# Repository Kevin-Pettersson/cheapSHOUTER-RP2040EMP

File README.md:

# cheapSHOUTER-RP2040EMP
Improved version of the great ChipSHOUTER-PicoEMP, this version has made cuts to the BOM and has added functionality inclduing: built in RP2040 instead of using a PICO, USB-C, LIPO charger + protection, USB isolation (not true isolation, allows to disconnect VBUS) + TVS diodes, buzzer, cleaner layout, and more.

## Contributors
- Colin O'Flynn (original HW design)
- Nezza (original FW)
- Kevin Pettersson 
- Linus Backlund
- Wilhelm Westermark

## Firmware
The firmware is a slightly tweaked version of the c-firmware from the original repo. The changes adapts the button logic to the active-high board design and activates the buzzer for a short period upon manual pulses.

## License

This work is licensed under a [Creative Commons Attribution-ShareAlike 3.0 International License][cc-by-sa].

[cc-by-sa]: http://creativecommons.org/licenses/by-sa/3.0/
[cc-by-sa-image]: https://licensebuttons.net/l/by-sa/3.0/88x31.png
[cc-by-sa-shield]: https://img.shields.io/badge/License-CC%20BY--SA%203.0-lightgrey.svg

ChipSHOUTER is a trademark of NewAE Technology Inc., registered in the US, European Union, and other jurisdictions.
PicoEMP is a trademark of NewAE Technology Inc.

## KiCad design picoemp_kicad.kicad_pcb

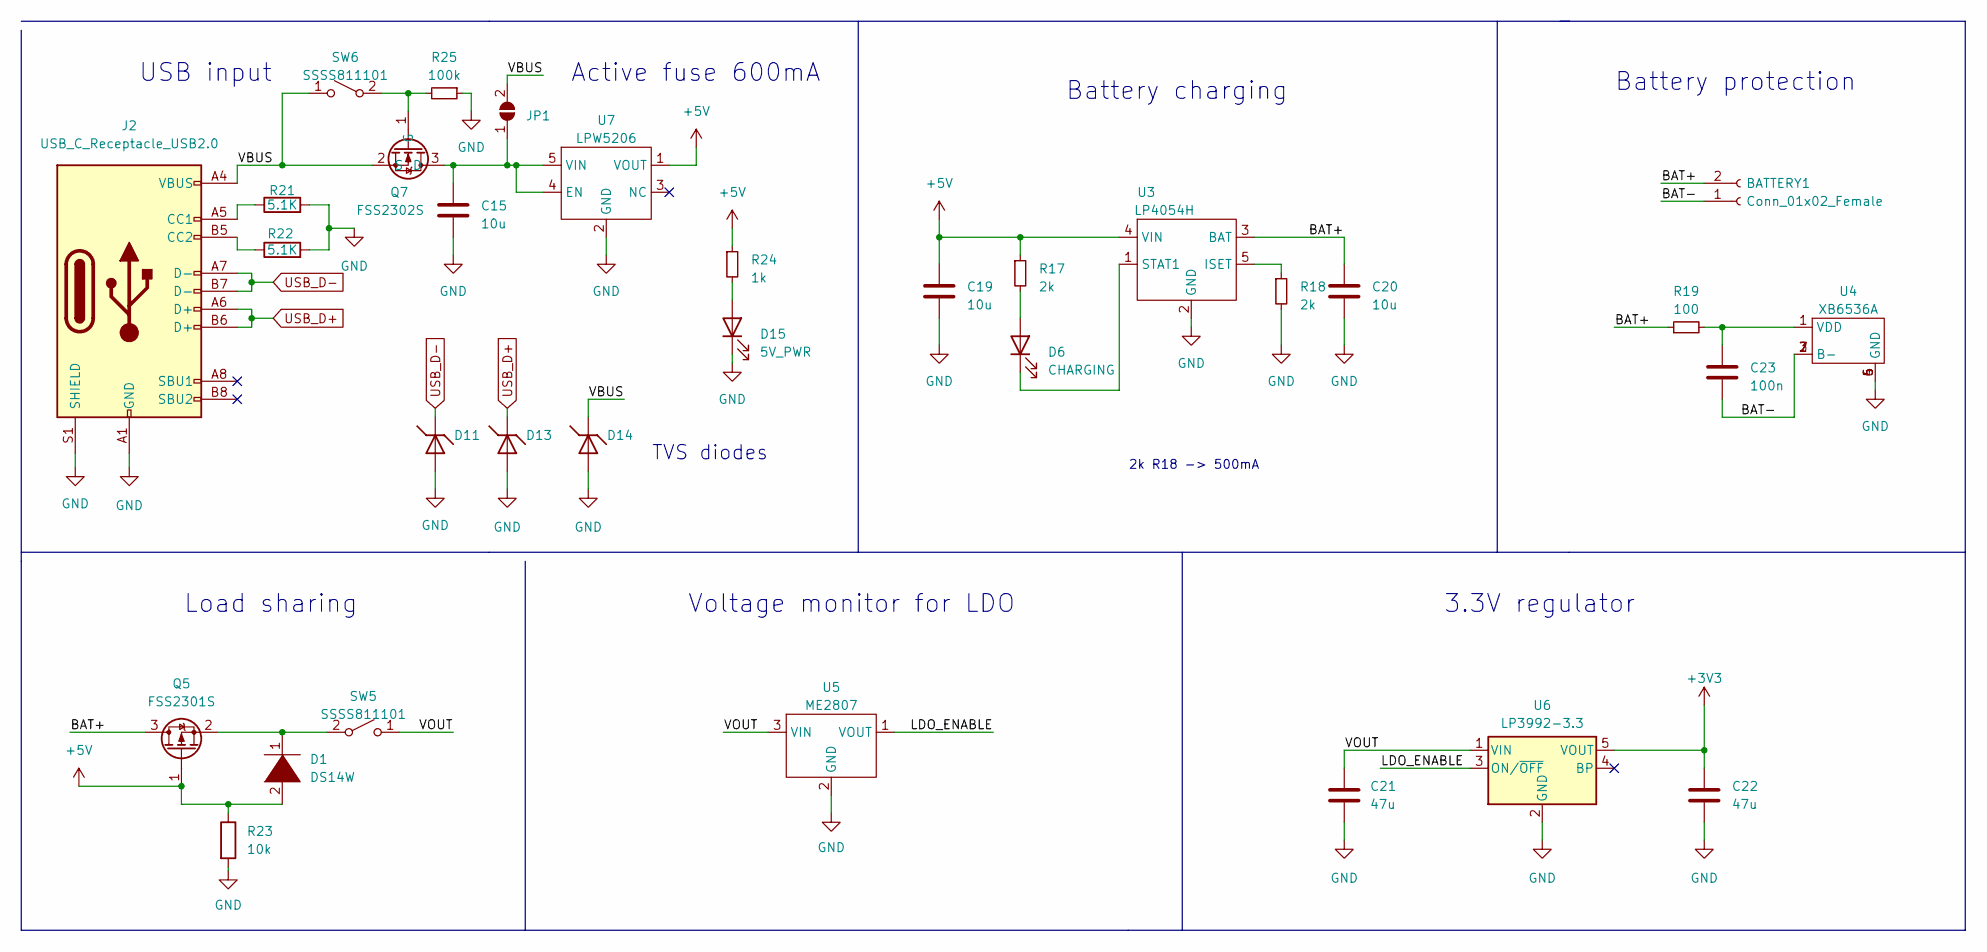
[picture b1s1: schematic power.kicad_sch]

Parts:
BATTERY1: Conn_01x02_Female; JST_PH_S2B-PH-K_1x02_P2.00mm_Horizontal
C15, C19, C20: 10u; C_0603_1608Metric
C21, C22: 47u; C_0805_2012Metric
C23: 100n; C_0603_1608Metric
D1: DS14W; D_SOD-123F
D6: CHARGING; LED_0603_1608Metric
D11, D13: LESD9L5.0T5G; D_SOD-923
D14: PESDNC5D7VU; D_SOD-523
D15: 5V_PWR; LED_0603_1608Metric
J2: USB_C_Receptacle_USB2.0; USB_C_Receptacle_HRO_TYPE-C-31-M-12; JLCPCB Part # C709357
JP1: SolderJumper-2_P1.3mm_Open_Pad1.0x1.5mm
Q5: FSS2301S; SOT-23
Q7: FSS2302S; SOT-23
R17, R18: 2k; R_0603_1608Metric
R19: 100; R_0603_1608Metric
R21: 5.1K; R_0603_1608Metric; JLCPCB Part # C23186
R22: 5.1K; R_0603_1608Metric
R23: 10k; R_0603_1608Metric
R24: 1k; R_0603_1608Metric
R25: 100k; R_0603_1608Metric
SW5, SW6: SSSS811101; SW_SPDT_PCM12
U3: LP4054H; SOT-23-5
U4: XB6536A; DFN-6-1EP_2x2mm_P0.65mm_EP1x1.6mm
U5: ME2807; SOT-23-3
U6: LP3992-3.3; SOT-23-5
U7: LPW5206; SOT-23-5

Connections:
+5V: C19.1, D1.2 (K), Q5.1 (G), R17.1, R23.1, R24.1, U3.4 (VIN), U7.1 (VOUT)
/Power/BAT+: BATTERY1.2 (Pin_1), C20.1, Q5.3 (D), R19.1, U3.3 (BAT)
/Power/BAT-: BATTERY1.1 (Pin_2), C23.2, U4.2 (B-), U4.3 (B-), U4.7 (B-)
/Power/LDO_ENABLE: U5.1 (VOUT), U6.3 (ON/~OFF)
/Power/VBUS: D14.1 (K), J2.A4 (VBUS), J2.A9 (VBUS), J2.B4 (VBUS), J2.B9 (VBUS), JP1.2 (B), Q7.2 (S), SW6.1 (B)
/Power/VOUT: C21.1, SW5.1 (B), U5.3 (VIN), U6.1 (VIN)
GND: C15.2, C19.2, C20.2, C21.2, C22.2, D11.2 (A), D13.2 (A), D14.2 (A), D15.1 (K), J2.A1 (GND), J2.A12 (GND), J2.B1 (GND), J2.B12 (GND), J2.S1 (SHIELD), R18.2, R21.2, R22.2, R23.2, R25.1, U3.2 (GND), U4.4 (GND), U4.5 (GND), U4.6 (GND), U5.2 (GND), U6.2 (GND), U7.2 (GND); also elsewhere on the board
unnamed: D1.1 (A), Q5.2 (S), SW5.2 (A)
unnamed: D6.2 (A), R17.2
unnamed: D6.1 (K), U3.1 (STAT1)
unnamed: D15.2 (A), R24.2
unnamed: J2.A5 (CC1), R21.1
unnamed: J2.B5 (CC2), R22.1
unnamed: Q7.1 (G), R25.2, SW6.2 (A)
unnamed: R18.1, U3.5 (ISET)
unnamed: C23.1, R19.2, U4.1 (VDD)
USB_D+: D13.1 (K), J2.A6 (D+), J2.B6 (D+); also elsewhere on the board
USB_D-: D11.1 (K), J2.A7 (D-), J2.B7 (D-); also elsewhere on the board

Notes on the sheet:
2k R18 -> 500mA
Battery protection
USB input
Battery charging
Voltage monitor for LDO
Active fuse 600mA
TVS diodes
3.3V regulator
Load sharing

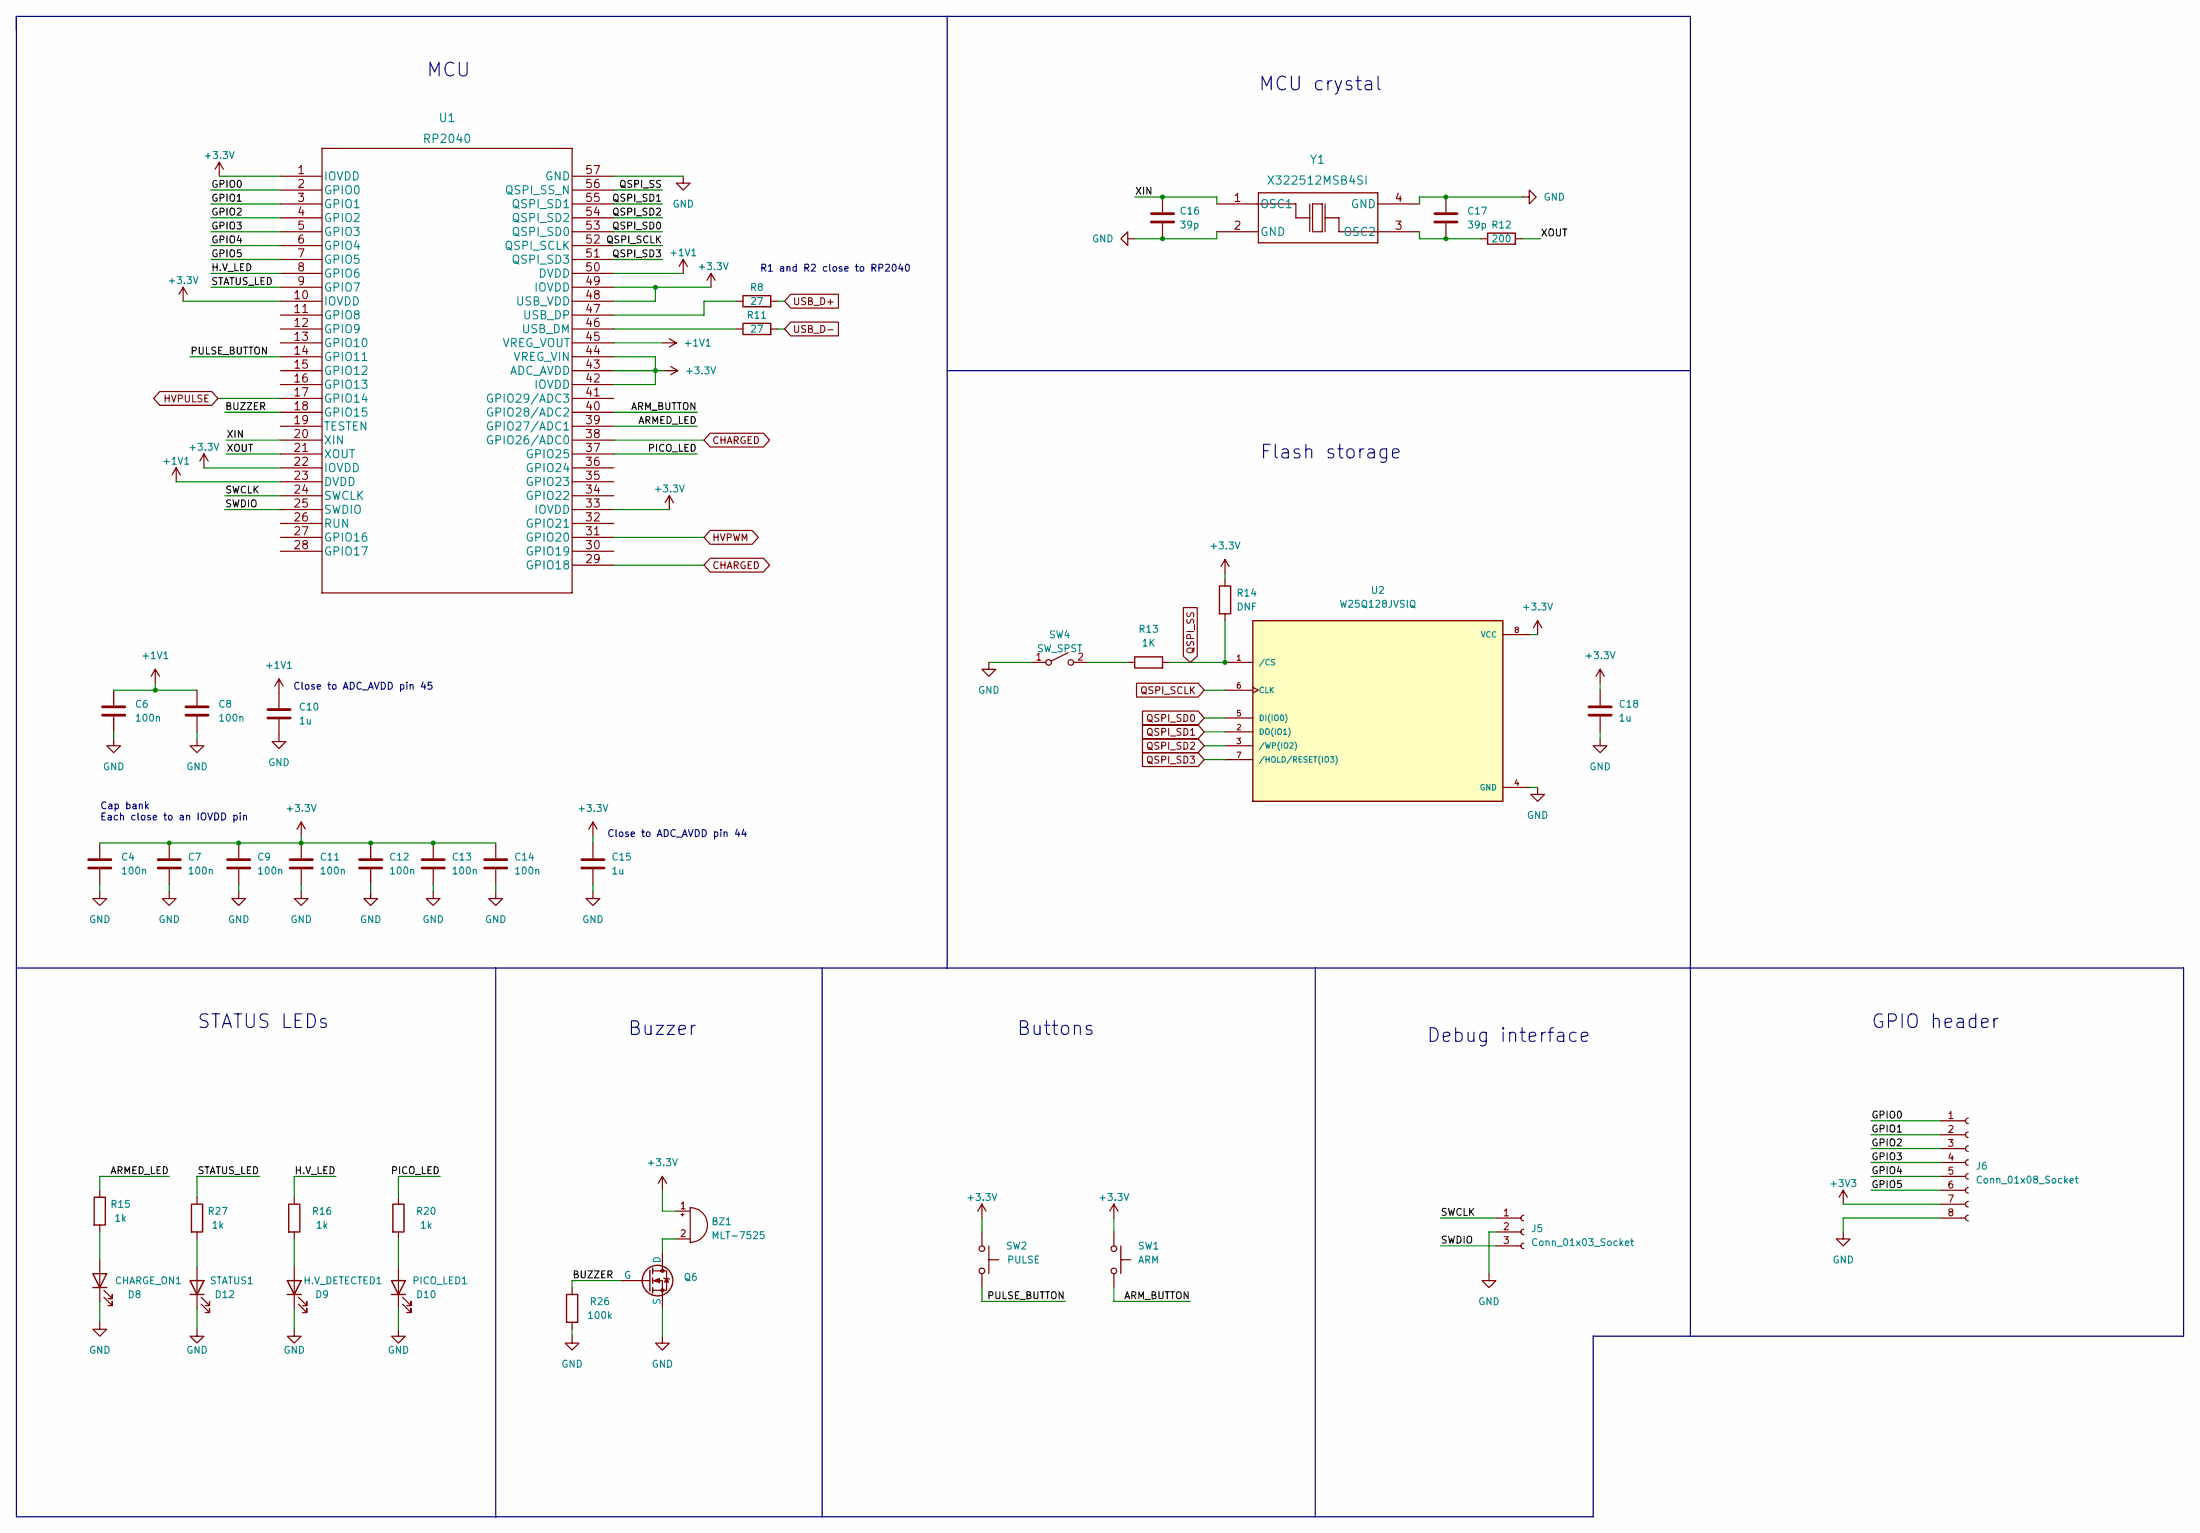
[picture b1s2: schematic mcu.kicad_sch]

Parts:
BZ1: MLT-7525; PUIAudio_SMT_0825_S_4_R
C4, C6, C7, C8, C9, C11, C12, C13, C14: 100n; C_0603_1608Metric
C10, C15, C18: 1u; C_0603_1608Metric
C16, C17: 39p; C_0603_1608Metric
D8: CHARGE_ON1; LED_0603_1608Metric
D9: H.V_DETECTED1; LED_0603_1608Metric
D10: PICO_LED1; LED_0603_1608Metric
D12: STATUS1; LED_0603_1608Metric
J5: Conn_01x03_Socket; PinHeader_1x03_P2.54mm_Vertical
J6: Conn_01x08_Socket; PinSocket_1x08_P2.54mm_Vertical
Q6: FSS2302S; SOT-23
R8, R11: 27; R_0603_1608Metric
R12: 200; R_0603_1608Metric
R13: 1K; R_0603_1608Metric
R14: DNF
R15, R16, R20, R27: 1k; R_0603_1608Metric
R26: 100k; R_0603_1608Metric
SW1: ARM
SW2: PULSE
SW4: SW_SPST; SW_SPST_CK_RS282G05A3
U1: RP2040; QFN-56-1EP_7x7mm_P0.4mm_EP3.2x3.2mm; JLCPCB Part # C2040
U2: W25Q128JVSIQ; IC_W25Q16JVUXIQ_TR; PARTREV I
Y1: X322512MSB4SI

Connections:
+1V1: C6.1, C8.1, C10.1, U1.23 (DVDD), U1.45 (VREG_VOUT), U1.50 (DVDD)
/RP2040/ARMED_LED: R15.1, U1.39 (GPIO27/ADC1)
/RP2040/ARM_BUTTON: SW1.1, U1.40 (GPIO28/ADC2)
/RP2040/BUZZER: Q6.1 (G), R26.1, U1.18 (GPIO15)
/RP2040/GPIO0: J6.1, U1.2 (GPIO0)
/RP2040/GPIO1: J6.2, U1.3 (GPIO1)
/RP2040/GPIO2: J6.3, U1.4 (GPIO2)
/RP2040/GPIO3: J6.4, U1.5 (GPIO3)
/RP2040/GPIO4: J6.5, U1.6 (GPIO4)
/RP2040/GPIO5: J6.6, U1.7 (GPIO5)
/RP2040/H.V_LED: R16.1, U1.8 (GPIO6)
/RP2040/PICO_LED: R20.1, U1.37 (GPIO25)
/RP2040/PULSE_BUTTON: SW2.2, U1.14 (GPIO11)
/RP2040/STATUS_LED: R27.1, U1.9 (GPIO7)
/RP2040/SWCLK: J5.1, U1.24 (SWCLK)
/RP2040/SWDIO: J5.3, U1.25 (SWDIO)
/RP2040/XIN: C16.1, U1.20 (XIN), Y1.1 (OSC1)
CHARGED: U1.29 (GPIO18), U1.38 (GPIO26/ADC0); also elsewhere on the board
GND: C4.2, C6.2, C7.2, C8.2, C9.2, C10.2, C11.2, C12.2, C13.2, C14.2, C15.2, C16.2, C17.1, C18.2, D8.1 (K), D9.1 (K), D10.1 (K), D12.1 (K), J5.2, J6.8, Q6.2 (S), R26.2, SW4.1 (A), U1.57 (GND), U2.4 (GND), Y1.2 (GND), Y1.4 (GND); also elsewhere on the board
HVPULSE: U1.17 (GPIO14); also elsewhere on the board
HVPWM: U1.31 (GPIO20); also elsewhere on the board
unnamed: BZ1.2 (-), Q6.3 (D)
unnamed: D8.2 (A), R15.2
unnamed: D9.2 (A), R16.2
unnamed: D10.2 (A), R20.2
unnamed: D12.2 (A), R27.2
unnamed: R13.1, SW4.2 (B)
unnamed: R11.1, U1.46 (USB_DM)
unnamed: R8.1, U1.47 (USB_DP)
QSPI_SCLK: U1.52 (QSPI_SCLK), U2.6 (CLK)
QSPI_SD0: U1.53 (QSPI_SD0), U2.5 (DI(IO0))
QSPI_SD1: U1.55 (QSPI_SD1), U2.2 (DO(IO1))
QSPI_SD2: U1.54 (QSPI_SD2), U2.3 (/WP(IO2))
QSPI_SD3: U1.51 (QSPI_SD3), U2.7 (/HOLD/RESET(IO3))
USB_D+: R8.2; also elsewhere on the board
USB_D-: R11.2; also elsewhere on the board

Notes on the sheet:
Cap bank Each close to an IOVDD pin
R1 and R2 close to RP2040
Buttons
MCU crystal
MCU
STATUS LEDs
Close to ADC_AVDD pin 45
Debug interface
Buzzer
Flash storage
Close to ADC_AVDD pin 44
GPIO header

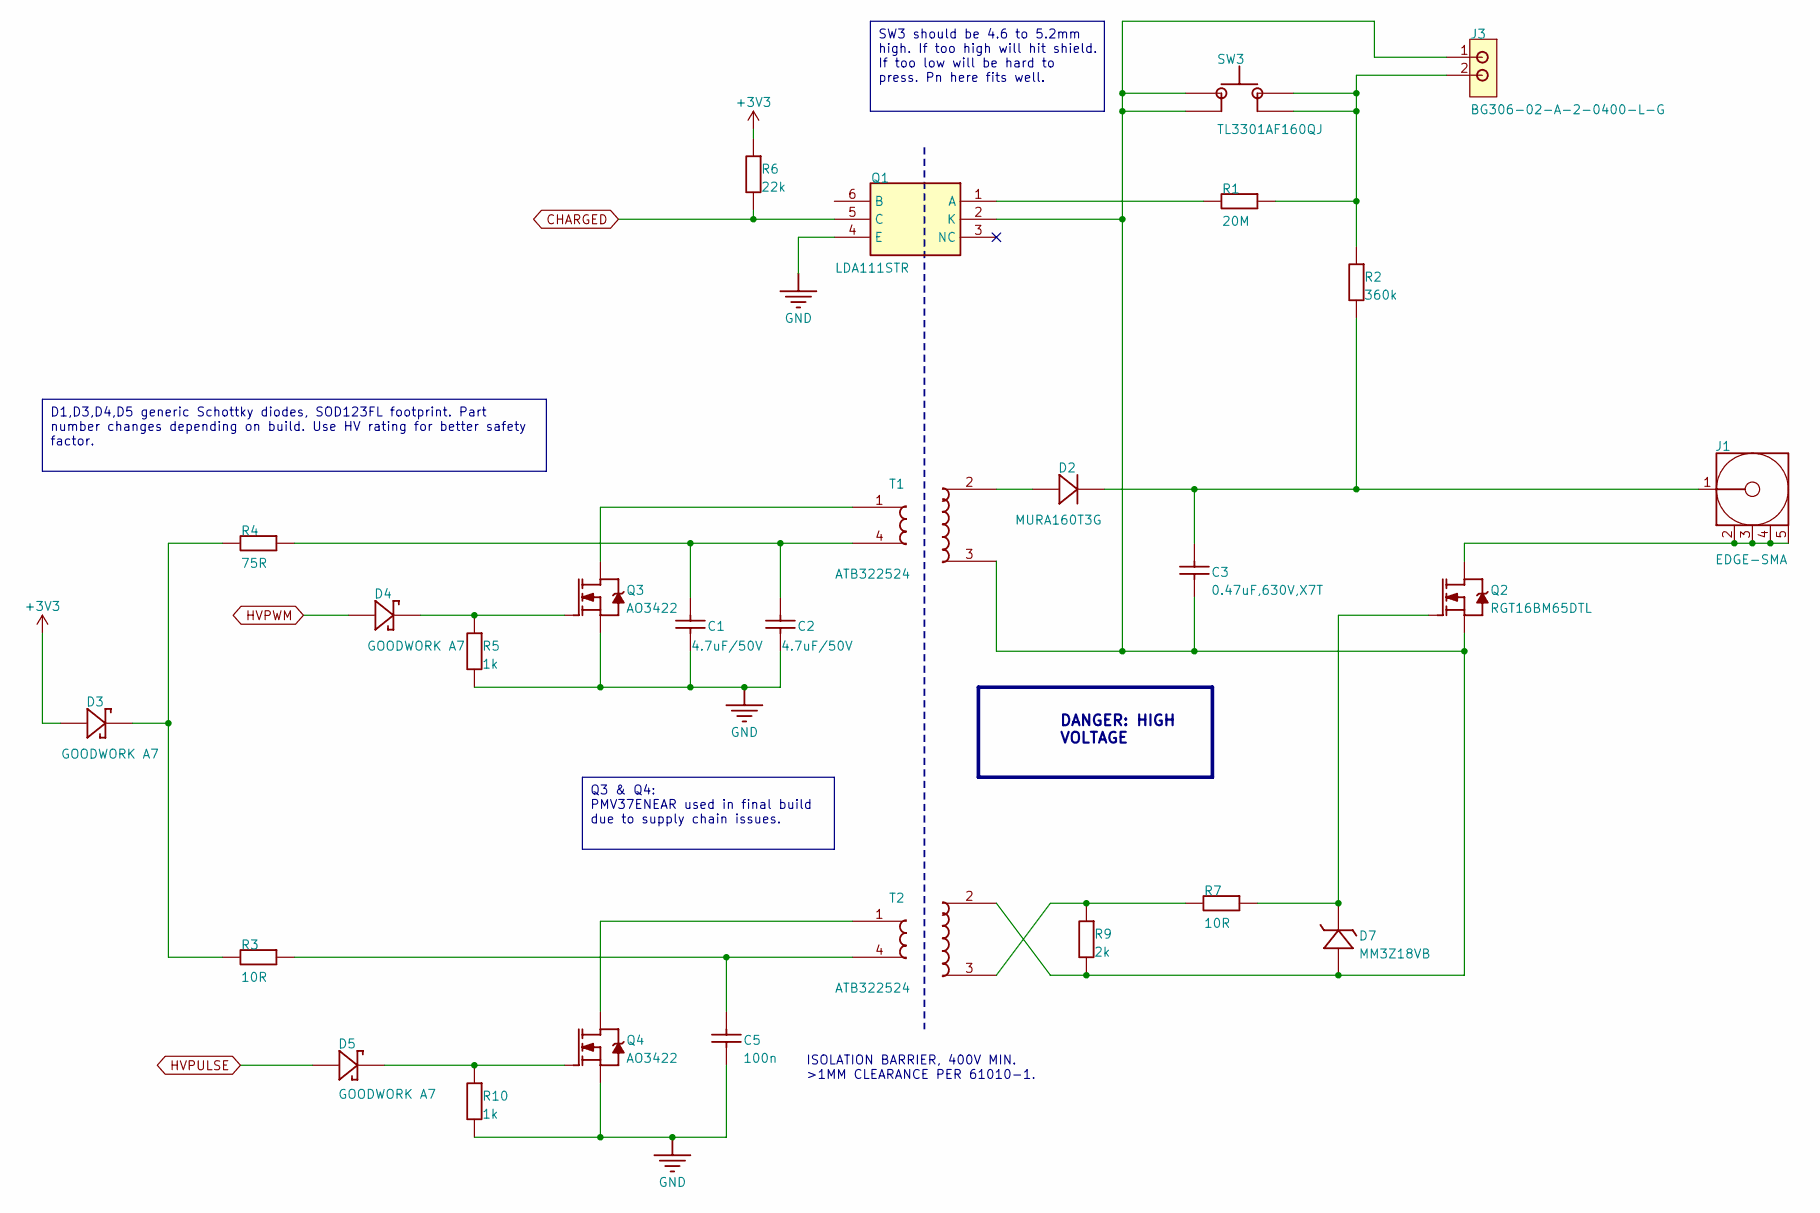
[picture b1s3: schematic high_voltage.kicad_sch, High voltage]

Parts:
C1, C2: 4.7uF/50V; CAPC0805_M; RATED VOLTAGE 50VDC; TOLERANCE 10%; PART NUMBER CCHIP-4u7-0805-50V
C3: 0.47uF,630V,X7T; C_2220_5650Metric; RATED VOLTAGE 630V; TOLERANCE +22/-30; PART NUMBER KRM55TR72J474MH01K
C5: 100n; CAPC0603_M; RATED VOLTAGE 50VDC; PART NUMBER CCHIP-100n-0603
D2: MURA160T3G; DO-214AC; RATED VOLTAGE 600V; PART NUMBER MURA160T3G
D3, D4, D5: GOODWORK A7; DSS13UTR; PART NUMBER DSS13UTR
D7: MM3Z18VB; SOD323; RATED VOLTAGE 10V; TOLERANCE 2%; PART NUMBER MM3Z18VB
J1: EDGE-SMA; CON-SMA-MALE-PCB-EDGE062; PART NUMBER CON-F-SMA-PCBEDGE-003.062
J3: BG306-02-A-2-0400-L-G; BG306-R2-2PIN; PART NUMBER BG306-02-A-2-0400-L-G
Q1: LDA111STR; _Users_colin_Documents_AltiumLL_SamacSys.PcbLib_SOP254P952X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; MANUFACTURER_PART_NUMBER LDA111STR; MOUSER PART NUMBER 849-LDA111STR
Q2: RGT16BM65DTL; DPAK_TO-252AA_M; RATED VOLTAGE 100V; PART NUMBER IRLR120TRPBF
Q3, Q4: AO3422; SOT95P245X110-3M; RATED VOLTAGE 30V; PART NUMBER DMN3200U-7
R1: 20M; RESC5025X06N; RATED VOLTAGE 400VDC; TOLERANCE 1%; PART NUMBER RCHIP-20M-2010
R2: 360k; RESC6432X06N; RATED VOLTAGE 250V; TOLERANCE 1%; PART NUMBER RCHIP-300K-2510
R3, R7: 10R; RESC1608X55N; RATED VOLTAGE 75VDC; TOLERANCE 1%; PART NUMBER RCHIP-10R-0603
R4: 75R; RESC2012X70N; RATED VOLTAGE 75VDC; TOLERANCE 1%; PART NUMBER RCHIP-75R-0805
R5, R10: 1k; RESC1608X55N; RATED VOLTAGE 75VDC; TOLERANCE 1%; PART NUMBER RCHIP-1K-0603
R6: 22k; RESC1608X55N; RATED VOLTAGE 75VDC; TOLERANCE 1%; PART NUMBER RCHIP-22K-0603
R9: 2k; RESC2012X70N; RATED VOLTAGE 75VDC; TOLERANCE 1%; PART NUMBER RCHIP-75R-0805
SW3: TL3301AF160QJ; CK_KSC7J; PART NUMBER TACTSW-KSC741J
T1, T2: ATB322524; ATB322524_CHUNKY; PART NUMBER ATB322524_PROTO

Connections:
CHARGED: Q1.5 (C), R6.2; also elsewhere on the board
GND: C1.2, C2.2, C5.2, Q1.4 (E), Q3.2 (S), Q4.2 (S), R5.2, R10.2; also elsewhere on the board
HVPULSE: D5.A; also elsewhere on the board
HVPWM: D4.A; also elsewhere on the board
unnamed: C1.1, C2.1, R4.2, T1.4
unnamed: C5.1, R3.2, T2.4
unnamed: D2.A, T1.2
unnamed: D3.K, R3.1, R4.1
unnamed: C3.1, D2.K, J1.1 (Signal), R2.2
unnamed: J3.2, R1.2, R2.1, SW3.2 (IN), SW3.3 (IN)
unnamed: Q1.1 (A), R1.1
unnamed: C3.2, D7.A, J3.1, Q1.2 (K), Q2.2 (S), R9.2, SW3.1 (IN), SW3.4 (IN), T1.3, T2.2
unnamed: J1.2 (GND), J1.3 (GND), J1.4 (GND), J1.5 (GND), Q2.3 (D)
unnamed: D7.K, Q2.1 (G), R7.2
unnamed: Q3.3 (D), T1.1
unnamed: D4.K, Q3.1 (G), R5.1
unnamed: Q4.3 (D), T2.1
unnamed: D5.K, Q4.1 (G), R10.1
unnamed: R7.1, R9.1, T2.3

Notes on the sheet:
Q3 & Q4: PMV37ENEAR used in final build due to supply chain issues.
D1,D3,D4,D5 generic Schottky diodes, SOD123FL footprint. Part number changes depending on build. Use HV rating for better safety factor.
SW3 should be 4.6 to 5.2mm high. If too high will hit shield. If too low will be hard to press. Pn here fits well.
ISOLATION BARRIER, 400V MIN. >1MM CLEARANCE PER 61010-1.
DANGER: HIGH VOLTAGE

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
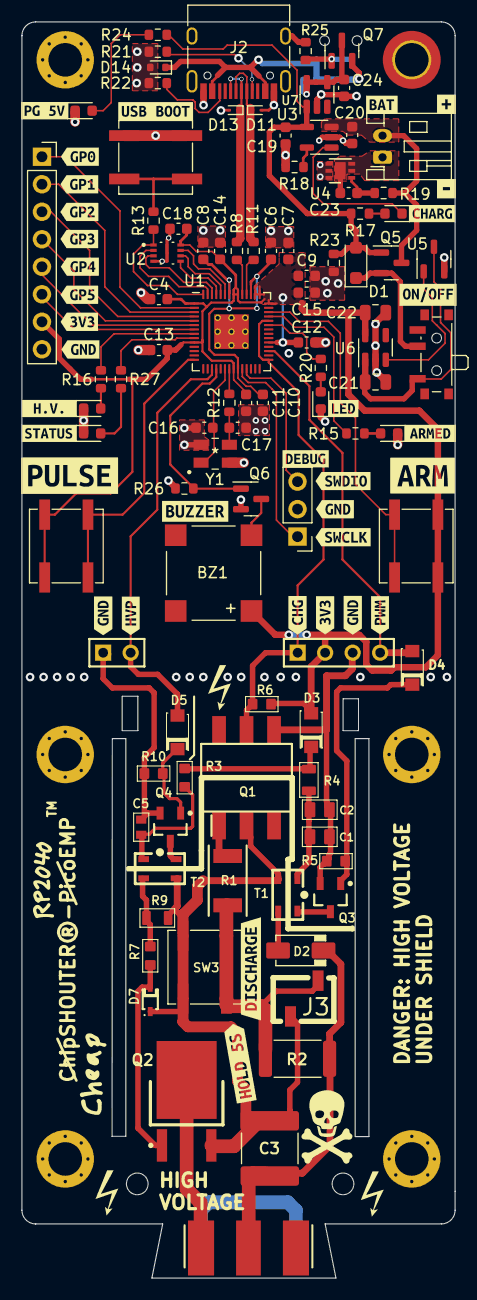
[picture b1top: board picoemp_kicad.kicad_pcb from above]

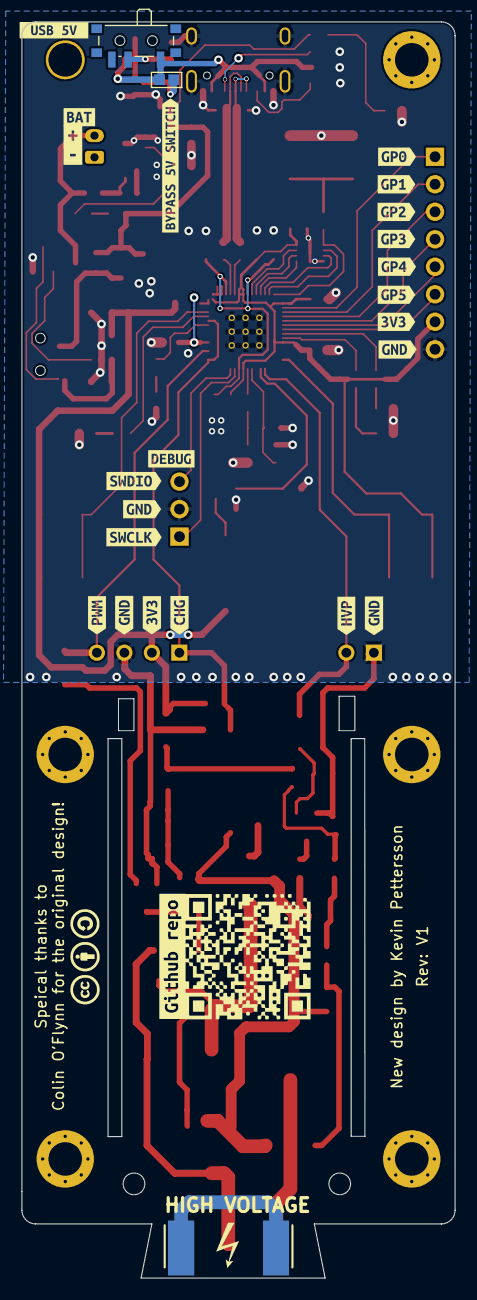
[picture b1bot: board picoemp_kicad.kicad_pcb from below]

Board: 2 copper layers, 40.0 x 116.0 mm, 161 parts (26 on the bottom side), 71 nets.

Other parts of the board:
C24: 10u; C_0603_1608Metric
MH1, MH1#2, MH1#3, MH1#4, MH1#5: M3, Tight Fit; _Users_colin_Dropbox (NewAE Technology Inc)_engineering_alt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
P2: Header 2; HDR1X2
P3: Header 4; HDR1X4
kibuzzard-63F26E53: G***; kibuzzard-63F26E53
kibuzzard-63F61A8A: G***; kibuzzard-63F61A8A
kibuzzard-63F78E1E, kibuzzard-63F78E1E#2: G***; kibuzzard-63F78E1E
kibuzzard-63F629BA: G***; kibuzzard-63F629BA
kibuzzard-63F668C9: G***; kibuzzard-63F668C9
kibuzzard-63F668D5: G***; kibuzzard-63F668D5
kibuzzard-63F668E9: G***; kibuzzard-63F668E9
kibuzzard-63F668EF: G***; kibuzzard-63F668EF
kibuzzard-63F668F6: G***; kibuzzard-63F668F6
kibuzzard-63F668FC: G***; kibuzzard-63F668FC
kibuzzard-63F2726C: G***; kibuzzard-63F2726C
kibuzzard-63F6135F, kibuzzard-63F6135F#2: G***; kibuzzard-63F6135F
kibuzzard-63F6689E: G***; kibuzzard-63F6689E
kibuzzard-63F65118: G***; kibuzzard-63F65118
kibuzzard-63F66756: G***; kibuzzard-63F66756
kibuzzard-63F66885: G***; kibuzzard-63F66885
kibuzzard-63FA0F3A: G***; kibuzzard-63FA0F3A
kibuzzard-63FA1A3D: G***; kibuzzard-63FA1A3D
kibuzzard-63FA16E2, kibuzzard-63FA16E2#2: G***; kibuzzard-63FA16E2
kibuzzard-63FA1685: G***; kibuzzard-63FA1685
kibuzzard-63FB3D52: G***; kibuzzard-63FB3D52
kibuzzard-63FB28A8: G***; kibuzzard-63FB28A8
kibuzzard-63FB28B5: G***; kibuzzard-63FB28B5
kibuzzard-63FB254D: G***; kibuzzard-63FB254D
kibuzzard-63FB255A: G***; kibuzzard-63FB255A
kibuzzard-63FB256F: G***; kibuzzard-63FB256F
kibuzzard-63FB271A, kibuzzard-63FB271A#2: G***; kibuzzard-63FB271A
kibuzzard-63FB287B: G***; kibuzzard-63FB287B
kibuzzard-63FB2541: G***; kibuzzard-63FB2541
kibuzzard-63FB2554: G***; kibuzzard-63FB2554
kibuzzard-63FB2562: G***; kibuzzard-63FB2562
kibuzzard-63FB2568: G***; kibuzzard-63FB2568
kibuzzard-63FB2575: G***; kibuzzard-63FB2575
kibuzzard-63FB2610, kibuzzard-63FB2610#2: G***; kibuzzard-63FB2610
kibuzzard-63FB2711, kibuzzard-63FB2711#2, kibuzzard-63FB2711#3, kibuzzard-63FB2711#4: G***; kibuzzard-63FB2711
kibuzzard-63FB2724, kibuzzard-63FB2724#2: G***; kibuzzard-63FB2724
kibuzzard-63FB2766, kibuzzard-63FB2766#2: G***; kibuzzard-63FB2766
kibuzzard-63FB2882: G***; kibuzzard-63FB2882
kibuzzard-63FB2887: G***; kibuzzard-63FB2887
kibuzzard-63FB2899: G***; kibuzzard-63FB2899
kibuzzard-63FF3009: G***; kibuzzard-63FF3009
kibuzzard-640062E5: G***; kibuzzard-640062E5
kibuzzard-640065CA: G***; kibuzzard-640065CA
kibuzzard-640384C5: G***; kibuzzard-640384C5
kibuzzard-640385A5: G***; kibuzzard-640385A5
kibuzzard-640461F9: G***; kibuzzard-640461F9
kibuzzard-6403912E: G***; kibuzzard-6403912E
kibuzzard-64031476: G***; kibuzzard-64031476

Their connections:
CHARGED: P3.1; also elsewhere on the board
GND: C24.2, P2.1, P3.3; also elsewhere on the board
HVPULSE: P2.2; also elsewhere on the board
HVPWM: P3.4; also elsewhere on the board

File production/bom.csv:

Designator,Footprint,Quantity,Value,LCSC Part #
"_2, ",,2,,
BATTERY1,JST_PH_S2B-PH-K_1x02_P2.00mm_Horizontal,1,Conn_01x02_Female,
BZ1,PUIAudio_SMT_0825_S_4_R,1,MLT-7525,
"C1, C2",_Users_cofly_Dropbox (NewAE Technology Inc)_engineering_altium_Libraries_footprints_CAPC0805_M.PcbLib_CAPC0805_M,2,4.7uF/50V,
C10,0603,1,1u,
C11,0603,1,100n,
C12,0603,1,100n,
C13,0603,1,100n,
C14,0603,1,100n,
C15,0603,1,1u,
C16,0603,1,39p,
C17,0603,1,39p,
C18,0603,1,1u,
C19,0603,1,10u,
C20,0603,1,10u,
C21,0805,1,47u,
C22,0805,1,47u,
C23,0603,1,100n,
C24,0603,1,10u,
C3,2220,1,"0.47uF,630V,X7T",
C4,0603,1,100n,
C5,_Users_cofly_Dropbox (NewAE Technology Inc)_engineering_altium_Libraries_footprints_CAPC0603_M.PcbLib_CAPC0603_M,1,100n,
C6,0603,1,100n,
C7,0603,1,100n,
C8,0603,1,100n,
C9,0603,1,100n,
D1,D_SOD-123F,1,DS14W,
D10,0603,1,PICO_LED1,
"D11, D13",D_SOD-923,2,LESD9L5.0T5G,
D12,0603,1,STATUS1,
D14,D_SOD-523,1,PESDNC5D7VU,
D15,0603,1,5V_PWR,
D2,_Users_cofly_Dropbox (NewAE Technology Inc)_engineering_altium_Libraries_footprints_DO-214AC.PcbLib_DO-214AC,1,MURA160T3G,
"D3, D4, D5",_Users_cofly_Dropbox (NewAE Technology Inc)_engineering_altium_NewAE_AltiumLib.DBLib/main_DSS13UTR,3,GOODWORK A7,
D6,0603,1,CHARGING,
D7,_Users_colin_Dropbox (NewAE Technology Inc)_engineering_altium_Libraries_footprints_SOD323.PcbLib_SOD323,1,MM3Z18VB,
D8,0603,1,CHARGE_ON1,
D9,0603,1,H.V_DETECTED1,
J1,_Users_cofly_Dropbox (NewAE Technology Inc)_engineering_altium_Libraries_footprints_CON-SMA-MALE-PCB-EDGE062.PcbLib_CON-SMA-MALE-PCB-EDGE062,1,EDGE-SMA,
J2,USB_C_Receptacle_HRO_TYPE-C-31-M-12,1,USB_C_Receptacle_USB2.0,C709357
J3,_Users_cofly_Dropbox (NewAE Technology Inc)_engineering_altium_Libraries_footprints_GCT_BG306.PcbLib_BG306-R2-2PIN,1,BG306-02-A-2-0400-L-G,
J5,PinHeader_1x03_P2.54mm_Vertical,1,Conn_01x03_Socket,
J6,PinSocket_1x08_P2.54mm_Vertical,1,Conn_01x08_Socket,
JP1,SolderJumper-2_P1.3mm_Open_Pad1.0x1.5mm,1,~,
"MH1_5, MH1_4, MH1_3, MH1_2, MH1",_Users_colin_Dropbox (NewAE Technology Inc)_engineering_altium_Libraries_footprints_MOUNT_M3_TIGHT.PcbLib_MOUNT_M3_TIGHT,5,"M3, Tight Fit",
P2,HDR1X2,1,Header 2,
P3,HDR1X4,1,Header 4,
Q1,SOP254P952X470-6N,1,LDA111STR,
Q2,_Users_cofly_Dropbox (NewAE Technology Inc)_engineering_altium_Libraries_footprints_DPAK_TO-252AA_M.PcbLib_DPAK_TO-252AA_M,1,RGT16BM65DTL,
"Q3, Q4",_Users_cofly_Dropbox (NewAE Technology Inc)_engineering_altium_Libraries_footprints_SOT95P245X110-3M.PcbLib_SOT95P245X110-3M,2,AO3422,
Q5,SOT-23,1,FSS2301S,
Q6,SOT-23,1,FSS2302S ,
Q7,SOT-23,1,FSS2302S,
R1,_Users_cofly_Dropbox (NewAE Technology Inc)_engineering_altium_NewAE_AltiumLib.DBLib/main_RESC5025X06N,1,20M,
"R10, R5",_Users_cofly_Dropbox (NewAE Technology Inc)_engineering_altium_Libraries_footprints_RESC1608X55N.PcbLib_RESC1608X55N,2,1k,
R11,0603,1,27,
R12,0603,1,200,
R13,0603,1,1K,
R15,0603,1,1k,
R16,0603,1,1k,
R17,0603,1,2k,
R18,0603,1,2k,
R19,0603,1,100,
R2,2512,1,360k,
R20,0603,1,1k,
R21,0603,1,5.1K,C23186
R22,0603,1,5.1K,
R23,0603,1,10k,
R24,0603,1,1k,
R25,0603,1,100k,
R26,0603,1,100k,
R27,0603,1,1k,
R3,_Users_cofly_Dropbox (NewAE Technology Inc)_engineering_altium_NewAE_AltiumLib.DBLib/main_RESC1608X55N,1,10R,
R4,_Users_cofly_Dropbox (NewAE Technology Inc)_engineering_altium_Libraries_footprints_RESC2012X70N.PcbLib_RESC2012X70N,1,75R,
R6,_Users_colin_Dropbox (NewAE Technology Inc)_engineering_altium_Libraries_footprints_RESC1608X55N.PcbLib_RESC1608X55N,1,22k,
R7,_Users_cofly_Dropbox (NewAE Technology Inc)_engineering_altium_Libraries_footprints_RESC1608X55N.PcbLib_RESC1608X55N,1,10R,
R8,0603,1,27,
R9,_Users_cofly_Dropbox (NewAE Technology Inc)_engineering_altium_Libraries_footprints_RESC2012X70N.PcbLib_RESC2012X70N,1,2k,
SW1,_Users_cofly_Dropbox (NewAE Technology Inc)_engineering_altium_Libraries_footprints_CK_KSC7J.PcbLib_CK_KSC7J,1,ARM,
SW2,_Users_cofly_Dropbox (NewAE Technology Inc)_engineering_altium_Libraries_footprints_CK_KSC7J.PcbLib_CK_KSC7J,1,PULSE,
SW3,_Users_colin_Dropbox (NewAE Technology Inc)_engineering_altium_Libraries_footprints_CK_KSC7J.PcbLib_CK_KSC7J,1,TL3301AF160QJ,
SW4,_Users_cofly_Dropbox (NewAE Technology Inc)_engineering_altium_Libraries_footprints_CK_KSC7J.PcbLib_CK_KSC7J,1,SW_SPST,
"SW5, SW6",SW_SPDT_PCM12,2,SSSS811101,
"T1, T2",_Users_cofly_Dropbox (NewAE Technology Inc)_engineering_altium_Libraries_footprints_ATB322524.PcbLib_ATB322524,2,ATB322524,
U1,QFN-56-1EP_7x7mm_P0.4mm_EP3.2x3.2mm,1,RP2040,C2040
U2,IC_W25Q16JVUXIQ_TR,1,W25Q128JVSIQ,
U3,SOT-23-5,1,LP4054H,
U4,DFN-6-1EP_2x2mm_P0.65mm_EP1x1.6mm,1,XB6536A,
U5,SOT-23-3,1,ME2807,
U6,SOT-23-5,1,LP3992-3.3,
U7,SOT-23-5,1,LPW5206,
Y1,X322512MSB4SI,1,X322512MSB4SI,

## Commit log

2023-02-20 Inital commit
2023-02-21 Swapped charging IC for reduced footprint
2023-02-26 finalized schematic + layout
2023-03-01 Small tweaks
2023-03-04 finishing touches
2023-03-05 Minor adjustment to silkscreen
2023-03-05 Minor adjustment silkscreen
2023-03-05 updated renders
2024-10-31 Add tweaked c-firmware

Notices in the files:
parts and their libraries:
Copyright 2021 Accelerated Designs. All rights reserved.
